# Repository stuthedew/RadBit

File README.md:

Radiation Bean
==============

Wearable Radiation sensor based off of LightBLue Bean and Teviso RD2007.
https://www.hackster.io/stuthedew/radbit-d8bf96

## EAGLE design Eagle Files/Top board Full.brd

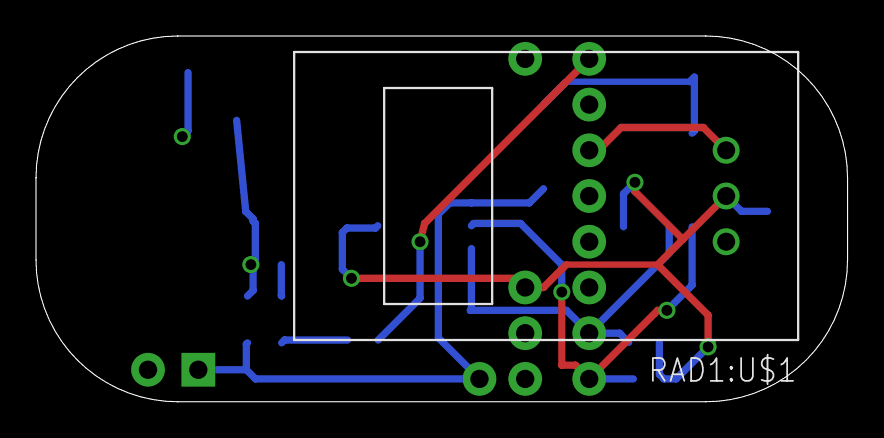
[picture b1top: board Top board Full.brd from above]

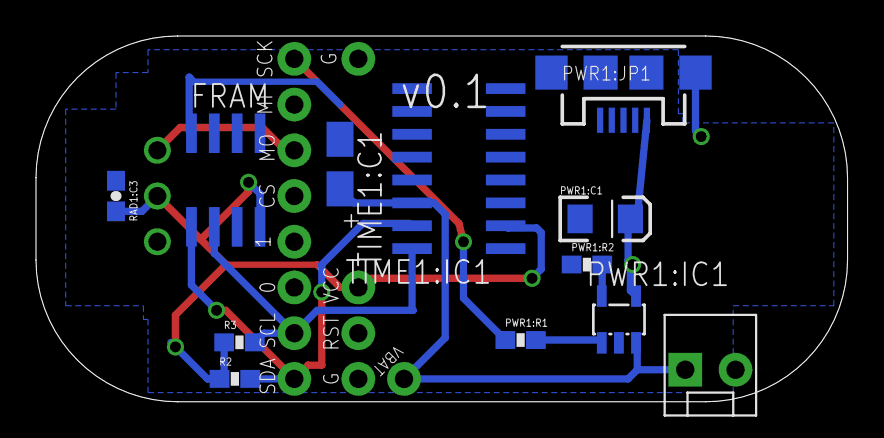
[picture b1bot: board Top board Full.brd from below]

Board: 2 copper layers, 45.1 x 20.3 mm, 26 parts (12 on the bottom side), 10 nets.

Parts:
0, 1, 2, 3, 4, 5: PROTO_POINT; 1X01
A0, A1: PROTO_POINT; 1X01
BAT: PROTO_POINT; 1X01
FRAM: MB85RC256V; SO08
GND@2, GND@3: PROTO_POINT; 1X01
PWR1:C1: 10uF; EIA3216
PWR1:IC1: MCP73831/OT; SOT23-5L
PWR1:JP1: USB-MICROB
PWR1:JP2: MOLEX-1X2_LOCK
PWR1:R1: 470; 0603-RES
PWR1:R2: 2000; 0603-RES
R2, R3: 10K; 0603-RES
RAD1:C3: 10pF; 0603-CAP
RAD1:U$1: RD2007
RESET: PROTO_POINT; 1X01
TIME1:C1: A/3216-18R
TIME1:IC1: DS3231; SO16
VCC: PROTO_POINT; 1X01

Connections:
CLK: 5.1, PWR1:R1.1
GND: FRAM.GND, GND@2.1, GND@3.1, PWR1:C1.C, PWR1:IC1.2, PWR1:JP1.GND, PWR1:JP1.MT1, PWR1:JP1.MT2, PWR1:JP2.2, PWR1:R2.1, RAD1:C3.1, RAD1:U$1.GND, TIME1:C1.-, TIME1:IC1.5, TIME1:IC1.6, TIME1:IC1.7, TIME1:IC1.8, TIME1:IC1.9, TIME1:IC1.10, TIME1:IC1.11, TIME1:IC1.12, TIME1:IC1.13
MOSI: 3.1, RAD1:U$1.OUT
PWR1:N$1: PWR1:IC1.1, PWR1:R1.2
PWR1:N$2: PWR1:IC1.5, PWR1:R2.2
PWR1:VBUS: PWR1:C1.A, PWR1:IC1.4, PWR1:JP1.VBUS
SCL: A1.1, FRAM.SCL, R3.2, TIME1:IC1.16
SDA: A0.1, FRAM.SDA, R2.2, TIME1:IC1.15
VBAT: BAT.1, PWR1:IC1.3, PWR1:JP2.1, TIME1:C1.+, TIME1:IC1.14
VCC: FRAM.VDD, R2.1, R3.1, RAD1:C3.2, RAD1:U$1.VCC, TIME1:IC1.2, VCC.1

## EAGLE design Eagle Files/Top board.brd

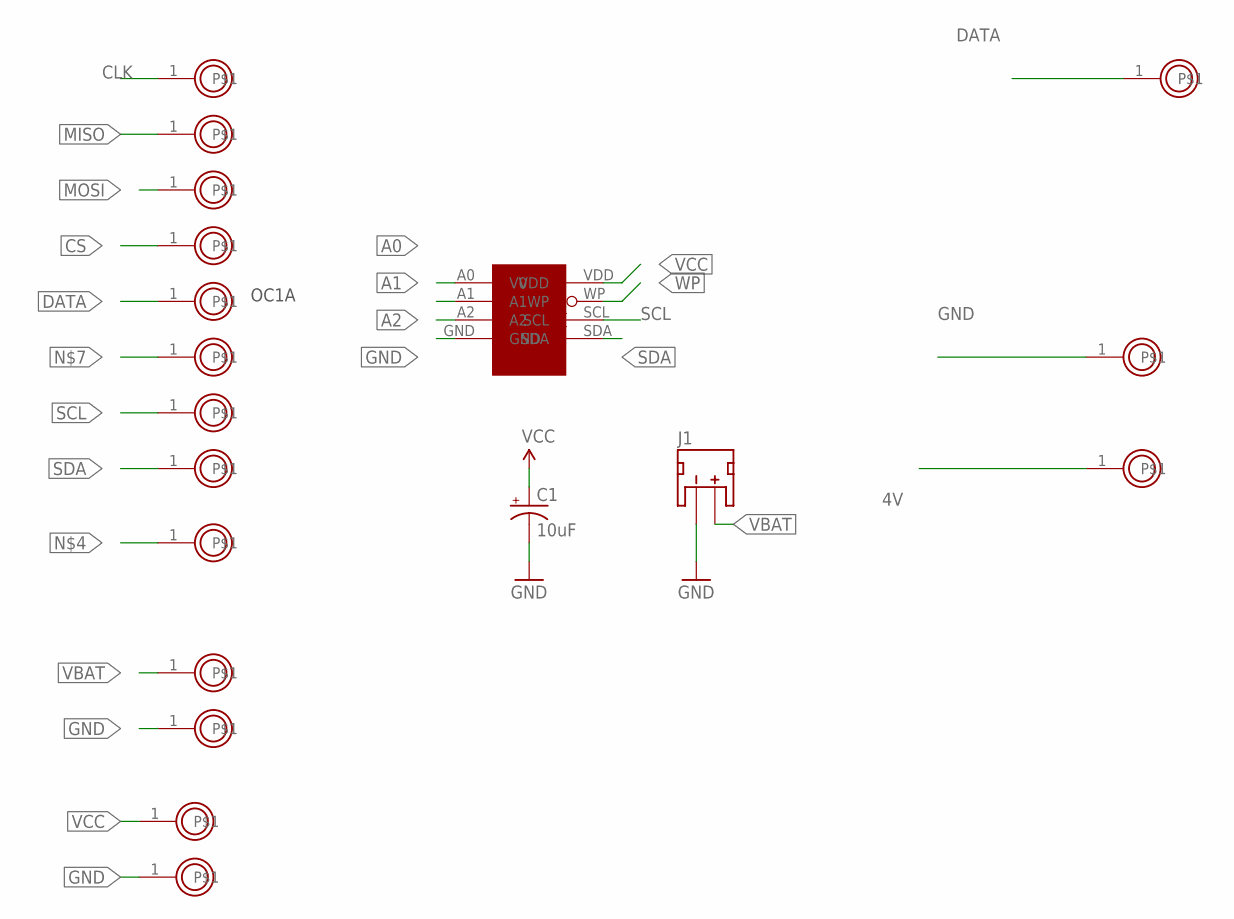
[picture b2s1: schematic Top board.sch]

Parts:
0, 1, 2, 3, 4, 4V, 5: PROTO_POINT; 1X01
A0, A1: PROTO_POINT; 1X01
BAT: PROTO_POINT; 1X01
C1: 10uF; EIA3216
DATA: PROTO_POINT; 1X01
FRAM: MB85RC256V; SO08
GND@1, GND@2, GND@3: PROTO_POINT; 1X01
J1: JST_2MM_MALE; JST-2-SMD
RESET: PROTO_POINT; 1X01
VCC: PROTO_POINT; 1X01

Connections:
4V: 4V.1
A0: FRAM.A0 (V0)
A1: FRAM.A1
A2: FRAM.A2
CLK: 5.1
CS: 2.1
DATA: 1.1, DATA.1
GND: C1.C (-), FRAM.GND, GND@1.1, GND@2.1, GND@3.1, J1.1 (-)
MISO: 4.1
MOSI: 3.1
SCL: A1.1, FRAM.SCL
SDA: A0.1, FRAM.SDA
VBAT: BAT.1, J1.2 (+)
VCC: C1.A (+), FRAM.VDD, VCC.1
WP: FRAM.WP

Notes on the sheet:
OC1A

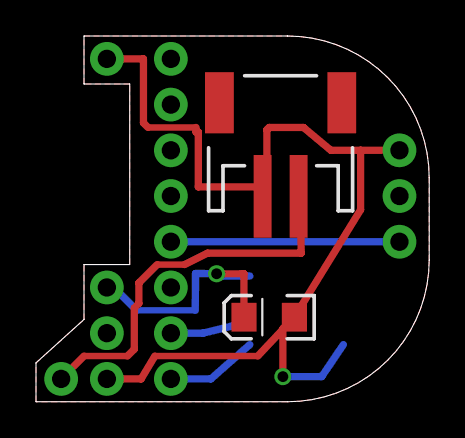
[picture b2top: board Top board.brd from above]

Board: 2 copper layers, 21.8 x 20.3 mm, 19 parts (1 on the bottom side), 6 nets.

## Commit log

2014-11-23 Create License
2014-11-23 Tweaks
2014-11-23 Tweak board
2014-11-26 Added board file
2014-11-26 V0.1 Top Board Finished
2014-11-26 Renamed Eagle files.
2014-11-26 Initial work on data structures.
2014-12-05 Tweak
2014-12-12 Modified gitignore to cover Eagle files
2014-12-12 v0.2
    Switched to 32KB I2C Fram.
2014-12-15 Board tweaks
2015-09-04 Misc Changes
2015-09-07 Create gh-pages branch via GitHub
2015-09-07 Added library.properties file
2015-09-07 Added keywords file
2015-09-07 Changed file names
2015-09-07 Added bit torrent sync files
2015-09-07 Deleted .bts files
2015-09-07 Added example folder and test file
2015-09-13 Updated year
2015-09-13 Config read/write working
2015-09-13 Worked on packet
2015-09-13 Worked on FRAM memory functions
2015-09-13 Packet design helper
2015-09-13 Debug and cleanup
2015-09-13 Clean up
2015-09-14 Added FRAM put command
2015-09-24 ignore btsc files
2015-09-24 Added iOS App
2015-09-24 updated .gitignore
2015-10-03 Added SOIC16 package
2015-10-03 Added RTC
2016-05-25 Fresh start
2016-05-25 Renamed Files
2016-05-25 Definitions
2016-05-25 LED Support
2016-05-25 Reworked INO file
2016-05-26 Beautify
2016-05-27 Added virtual functions for storage
2016-05-27 Implemented virtual functions
2016-05-27 Added sensor files
2017-02-16 Working
2017-02-17 Added temp iterator
2017-02-17 Clean-up
2017-02-17 Revert "Clean-up"
    This reverts commit b951b0d38e84e100616038ecae9643f75baad7f1.
2017-02-17 Revert "Revert "Clean-up""
    This reverts commit 1f4760be7c4600256830db4ca0ddd4035efdf617.
2017-02-17 Added Node-Red
2017-02-18 Added node red syncing
2017-02-19 Clean up and rename
2017-02-20 Abstracted Storage class
2017-02-20 Cleaned up classes
2017-02-20 Ignore Node-Red backups
2017-02-20 Removed RTC from schematic since no longer used
2017-02-20 Added "no new data" output
2017-02-22 Fixed skipped data bug
2017-03-29 Added 0.01uF Cap
    Added 0.01uF Cap to sensor GND and VCC pins to filter EMI from
    bluetooth.
2017-03-29 Node update
2017-03-29 Ignore btsync files
2017-03-29 Node stuff
2017-03-29 Added pulse width detect to rad sensor pin
    Attempt to filter out spurious signals.
2017-06-05 Radiation example chart
2017-06-05 Rename chart file
2017-11-22 ignore .rsl* files
2017-11-22 Revert "Tweaks"
    This reverts commit 8ffe56e48448ffa22b62120e7bc8eac18687d975.

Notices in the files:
parts and their libraries:
SparkFun-Capacitors: Licensing: Creative Commons ShareAlike 4.0 International - https://creativecommons.org/licenses/by-sa/4.0
